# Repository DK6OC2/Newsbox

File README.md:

# Newsbox
**05.03.2024** Stromlaufplan komplett überarbeitet </p>
**29.02.2024** Stromlaufplan Anpassung Anschluss Piezosummer </p>
**25.02.2024** Stromlaufplan hinzugefügt</p>
**21.02.2024** Gehäuse Prototyp für 3D Druck: https://www.thingiverse.com/thing:72719</p>
**01.02.2024** Der Programmcode ist jetzt in der main.cpp</p>

JSon-Format (aktuelle Version)
{
 "ID": 1111111,  //long int
 "Datum": "30.03.2024",
 "Message": {
    "Topic": "Topic", //9 Zeichen
    "Zeile1": "line1", //20 Zeichen
    "Zeile2": "line2", //20 Zeichen
    "Zeile3": "line3" //20 Zeichen
             }
}

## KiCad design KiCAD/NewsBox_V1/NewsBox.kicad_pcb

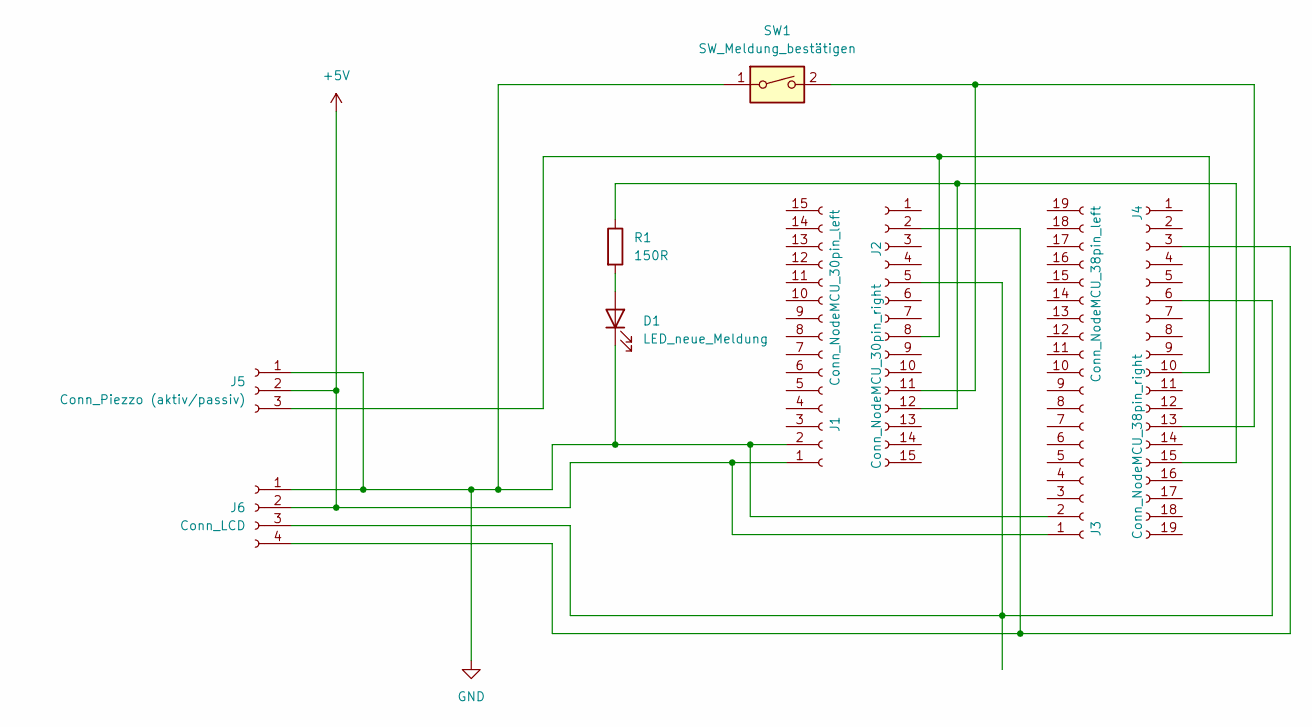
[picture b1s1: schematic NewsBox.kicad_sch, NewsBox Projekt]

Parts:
D1: LED_neue_Meldung; PinSocket_1x02_P2.54mm_Vertical
J1: Conn_NodeMCU_30pin_left; PinSocket_1x15_P2.54mm_Vertical
J2: Conn_NodeMCU_30pin_right; PinSocket_1x15_P2.54mm_Vertical
J3: Conn_NodeMCU_38pin_left; PinSocket_1x19_P2.54mm_Vertical
J4: Conn_NodeMCU_38pin_right; PinSocket_1x19_P2.54mm_Vertical
J5: Conn_Piezzo (aktiv/passiv); PinSocket_1x03_P2.54mm_Vertical
J6: Conn_LCD; PinSocket_1x04_P2.54mm_Vertical
R1: 150R; R_Axial_DIN0207_L6.3mm_D2.5mm_P10.16mm_Horizontal
SW1: SW_Meldung_bestätigen; PinSocket_1x02_P2.54mm_Vertical

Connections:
+5V: J1.1, J3.1, J5.2, J6.2
GND: D1.1 (K), J1.2, J3.2, J5.1, J6.1, SW1.1
unnamed: D1.2 (A), R1.2
unnamed: J2.2, J4.3, J6.4
unnamed: J2.5, J4.6, J6.3
unnamed: J2.8, J4.10, J5.3
unnamed: J2.11, J4.13, SW1.2
unnamed: J2.12, J4.15, R1.1

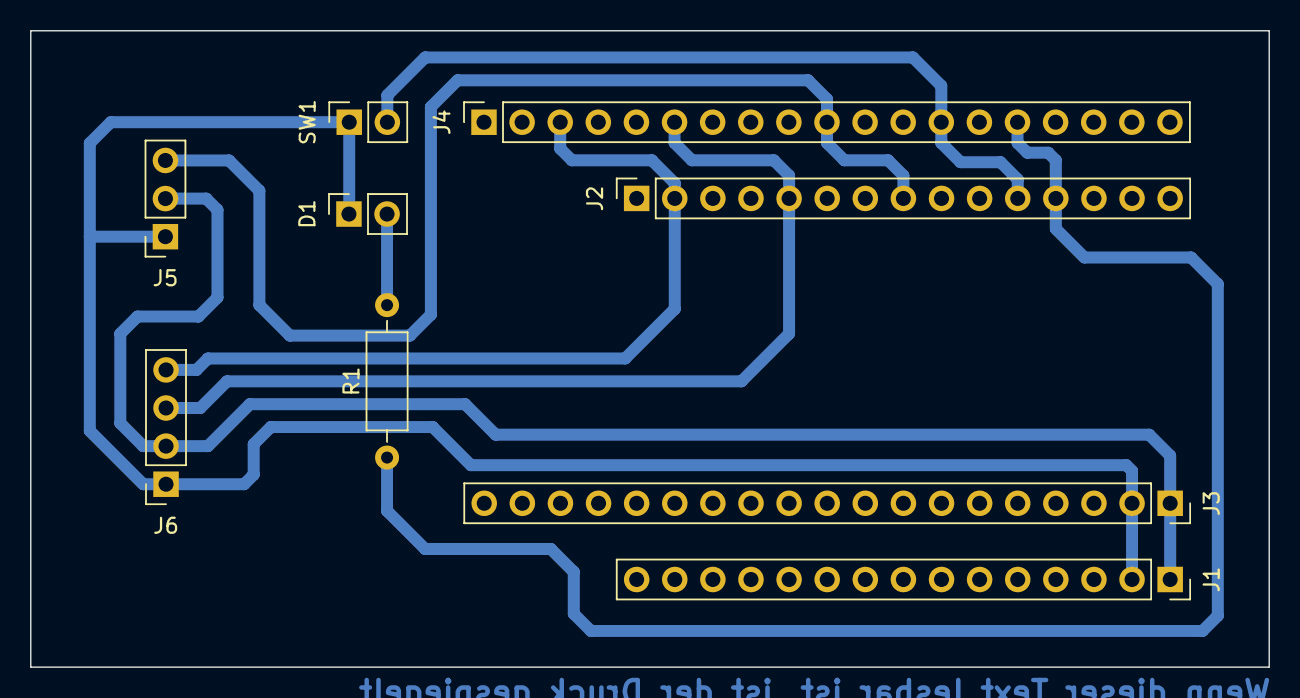
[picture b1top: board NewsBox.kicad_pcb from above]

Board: 2 copper layers, 82.6 x 42.4 mm, 9 parts (0 on the bottom side), 8 nets.

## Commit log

2024-02-08 first commit, setting up folder
2024-02-08 added Productplan
2024-02-08 DK6OC-Skript-20240206_2319.cpp aktualisieren
    Ergänzung einiger Ideen als Kommentar
2024-02-09 Create config.h
    Verschieben der Konfiguration in extra Datei
2024-02-09 Umsetzung der Verbesserungsvorschläge in die main.cpp-Datei
2024-02-10 So jetzt läuft das, allerdings ist auf dem Server bisher keine Nachricht
2024-02-10 config.h anonymising
2024-02-10 vscode erweiterungen
2024-02-10 Update .gitignore
    Ich hoffe das funktioniert
2024-02-10 Hm... keine ahnung was hier passiert ist
2024-02-10 main.cpp aktualisieren
    Kommentar ergänzt
2024-02-10 README.md aktualisieren
2024-02-10 einige Denkfehler korrigiert SSL-Zertifikat eingebunden
2024-02-10 main.cpp aktualisieren
    Bugfix und Kommentare ergänzt
2024-02-11 main.cpp aktualisieren
    Fehler beseitigt
2024-02-11 ignoriere SSL
2024-02-11 DHCP-Test und Print Mac
2024-02-11 Aufräumen nach Umstellung auf DHCP und "unsicheres" HTTPS
2024-02-11 main.cpp aktualisieren
    Leerstelle entfernt
2024-02-11 Update main.cpp
    Anpassung Display 2 Zeilen zu 4 Zeilen
2024-02-11 4 Zeilen Display und wiederholtes Trennen am ";"
2024-02-11 added config.h.example, config.h should not be included into repo
2024-02-11 multiple platforms
2024-02-11 md war nicht korrekt formartiert
2024-02-11 Update config.h
    Change URL of info.txt
2024-02-17 Umstellung auf JSon-Nachricht LED bei neuer Nachricht, wird nach Tastendruck ausgeschaltet
2024-02-18 Call im GET-Request
2024-02-18 initiale erstellung der WebServer Software
2024-02-18 erweitert um public_html verzeichnis
2024-02-18 updated, der aufruf der settings funktioniert
2024-02-24 Buzzer bei neuer Nachricht
2024-02-24 lausch.json
2024-02-25 Stromlaufplan mit LED, Summer und Reset
2024-02-25 Korrektur Farben für 3,3 Volt
2024-02-26 update webserver
2024-02-29 Anpassung Anschluss Piezosummer
    Anpassung Anschluss Piezosummer
2024-03-01 Anpassung Code für unterschiedliche Hardware
2024-03-02 Hardwareauswahl Display 0,96; 1,3 Zoll oder 20/4
2024-03-02 Code für Aktiv-Buzzer ergänzt
2024-03-03 server update
2024-03-03 webserver update
2024-03-04 Erster Entwurf für PCB
2024-03-05 Kommentar und Splash-Message ergänzt und Codecleaning
2024-03-05 Rev. 2, Komplette Überarbeitung,
    komplette Überarbeitung
    OLED Displays aufgenommen
2024-03-06 Überlegungen zu verschiedenen WLANS
2024-03-06 Fehleranzeige bei "kaputter" Nachricht
2024-03-06 Rückgängig mehrere WLANs
2024-03-06 main.cpp aktualisieren
    Bugfix
2024-03-06 Layout-Datei zum ätzen für Dieter erzeugt
2024-03-06 noch ein PDF zum Ätzen gemacht
2024-03-07 Multi-Wifi in progress not working yet
2024-03-07 Readme
2024-03-07 MultiWifi für biszu 5 Netze
2024-03-09 Anpassung Variablennamen (line statt zeile)
2024-03-10 fehlerhaft
2024-03-10 bugfix
2024-03-10 rm launch
2024-03-10 rm platformio.ini
2024-03-10 restore
2024-03-10 Anpassung Displayposition
2024-03-10 config.h
2024-03-10 umbennen von lib nach inc, weil plesk lib nicht erlaubt
2024-03-10 webserv update
2024-03-10 Update README.md to md Syntax
2024-03-10 Webserver/OLED
    - Anpassungen am Webserver durchgeführt (getestet auf Klaus Server)
    - OLED mit SSD1306 Controller hinzugefügt
2024-03-10 PINs wieder angepasst für az-delivery-devkit-v4
2024-03-10 html title tag added for each page
2024-03-10 added NOW_DISP for Date in Display
2024-03-10 not registred msg translated to english
2024-03-10 improve create msg form
2024-03-11 Display Font, Webserver
    - Andere Displayfont für OLED eingestellt
    - Webserver gibt jetzt ID der DB aus - somit können neue Einträge in der DB erkannt werden
2024-03-11 Webserver / Newsbox
    - Kleine Anpassungen an der message.php - Datum wird jetzt in deutscher Schreibweise ausgegeben
    - main.cpp - I2C PINs werden jetzt in der config.h definiert (siehe config.h.example!)
2024-03-11 ***-Signal für Nachrichtenabruf
2024-03-16 Anpassung Code an Json-File für Produktiv-System
2024-03-17 mods
2024-03-17 EPaper-Display
2024-03-17 Weitere Anpassungen für EPaper-Display
2024-03-18 added local platformio.ini file
2024-03-24 NOW_ISO ersetzt durch DB Function datetime(now)
2024-03-27 VSCode extensions eingepflegt
2024-03-29 vs code extensions, dass sollte fuer alle die gleiche sein
2024-03-29 vs code extension added ftp-simple
2024-03-29 fix validfrom input field
2024-03-29 add topics page
2024-03-29 dashboard and messages page added
2024-03-30 1. release
    meine erste version
2024-03-30 Json-Format in der Readme ergänzt
2024-03-30 JSon-Formate ergänzt in Readme
2024-03-30 multiple json test file added
2024-03-30 2.0 Branch anglegt für die Umsetzung der besprochenen Erweiterungen (Displaylibraries und WIFI-Manager)
2024-03-30 beardbeitung
2024-03-30 BEarbeitung, noch fehlerhaft
2024-03-30 noch fehlerhaft
2024-03-30 platformio.ini aktualisieren
2024-04-01 webserver update ...
2024-04-04 Auslagerung der Displaysteuerung Beispiel für Epaper29_bw funktioniert bereits
2024-04-04 Displayfile für 20/4-Display und Teplate für Displayfile
2024-04-06 Test für 4 color Epaper, noch nicht erfolgreich
2024-04-06 LCD20/04 Display
2024-04-06 Code für 20/04 Display angepasst Platformio für Bord+Display struckturiert Button-Events: click = Nachrichten weiterschalten halten = LED aus
2024-04-06 Displayauswahl über Build-Flag in der Platformio.ini EPaper-Display jetzt mit Anzeige der Überschrift (subject) Anzahl der Nummer der Nachricht und der Gesamtzahl der Nachrichten im Paket auf dem EPa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
2024-04-06 Bugfix weiterer Display Code
2024-04-07 Ergänzungen: Weiterer Displaycode Workaround für Buzzerbug beim Lilygo-t-display-s3 Verschiebung der Hardwareconfig in die Platformio.ini
2024-04-07 kleine Anpassung am Displaycode
2024-04-12 WifiManager eingebaut
    Es muss unter PlatformIO beim ersten Mal kompilieren der Punkt unter "PLATFORM -> Erase Flash and Upload" ausgewählt werden, damit auch die Datenpartition übertragen wird
2024-04-13 kleinere Anpassungen
    Das Passwort wird nicht mehr auf der Konsole ausgegeben
    Die Texte auf der Konsole wurde angepasst, damit sie besser lesbar sind
    Der WifiManager versucht jetzt 30 Sekunden das WiFi zu verbinden
2024-04-21 Funktion "display_wifi_connercting()" obsolet Display_code angepasst bugfix
    Achtung: Beim ersten Mal "Upload Filesystem erforderlich!"
2024-04-27 Neues Board ESP32-1732S019
2024-10-07 Neues Borad: esp32-1732S019
